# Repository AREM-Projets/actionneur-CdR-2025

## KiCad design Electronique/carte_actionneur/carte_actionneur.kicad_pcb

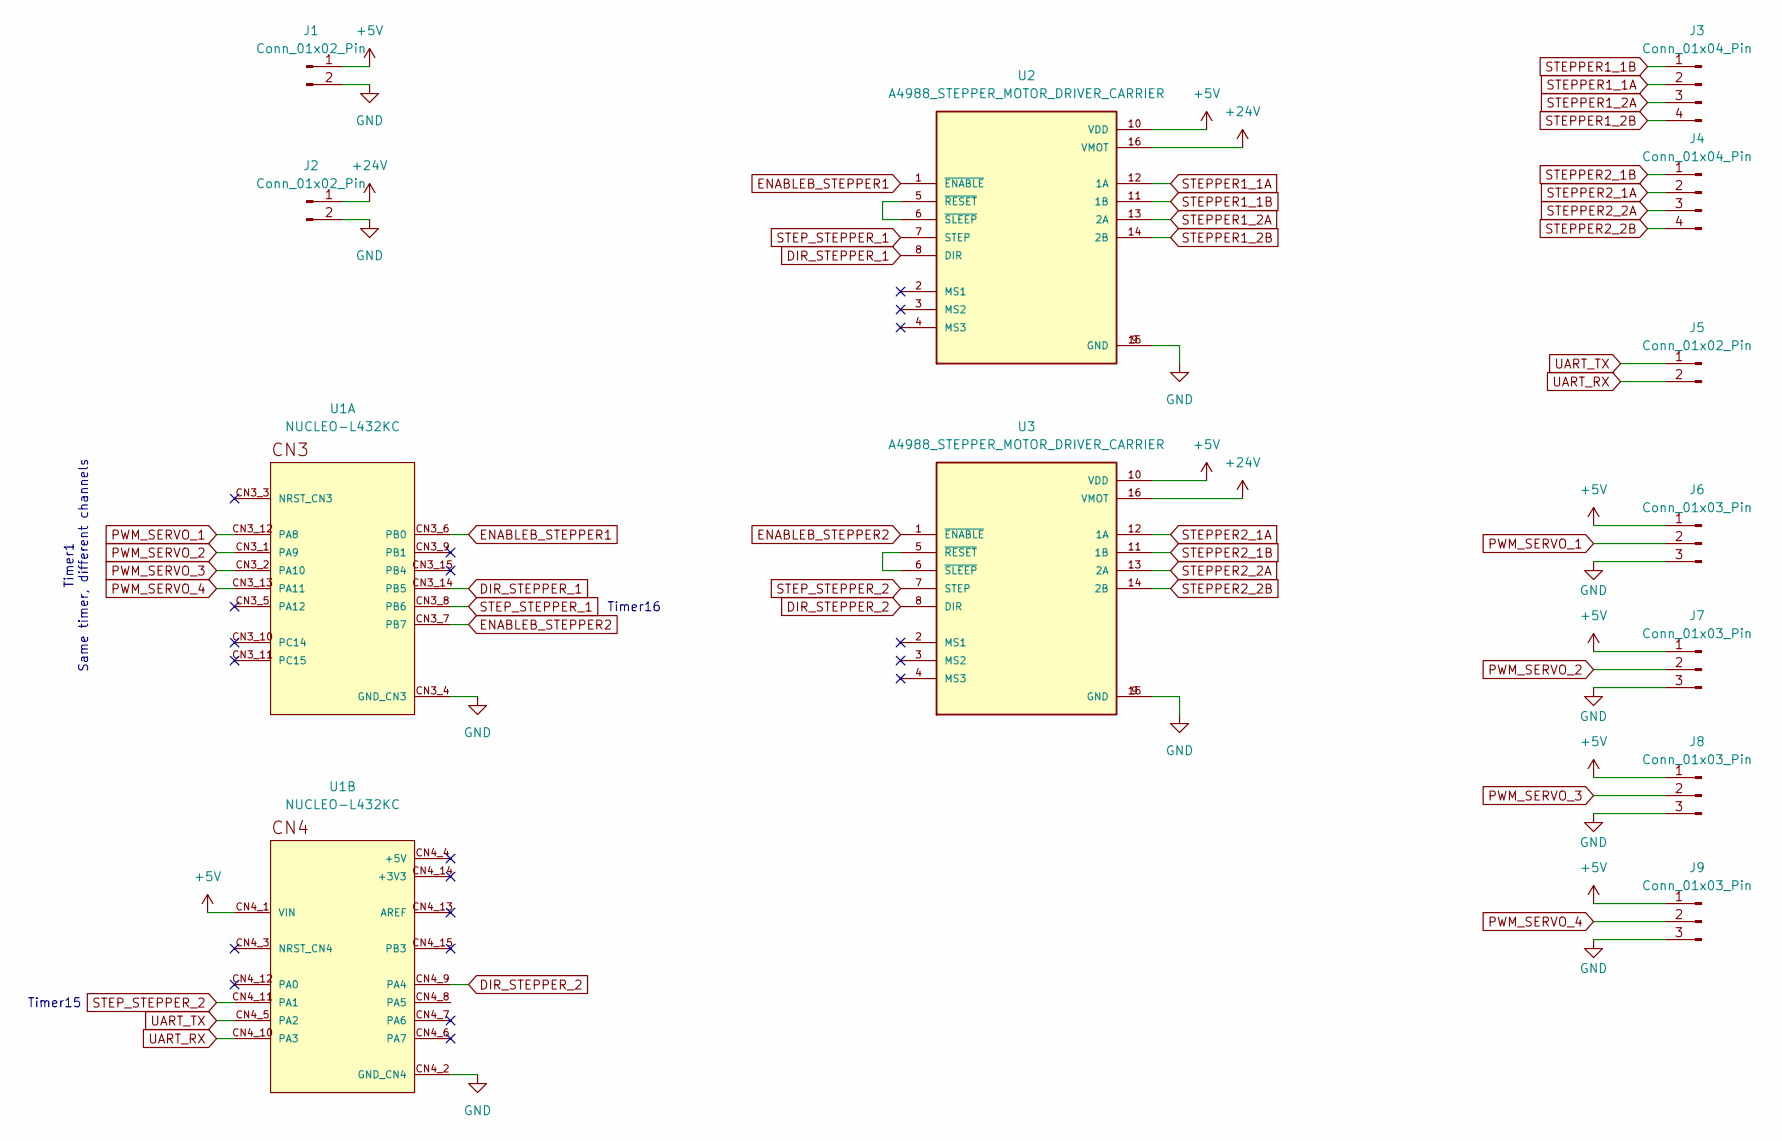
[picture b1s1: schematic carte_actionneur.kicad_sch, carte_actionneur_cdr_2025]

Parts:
J1, J2, J5: Conn_01x02_Pin; JST_EH_B2B-EH-A_1x02_P2.50mm_Vertical
J3, J4: Conn_01x04_Pin; JST_EH_B4B-EH-A_1x04_P2.50mm_Vertical
J6, J7, J8, J9: Conn_01x03_Pin; JST_EH_B3B-EH-A_1x03_P2.50mm_Vertical
U1: NUCLEO-L432KC; MODULE_NUCLEO-L432KC; PARTREV N/A
U2, U3: A4988_STEPPER_MOTOR_DRIVER_CARRIER; MODULE_A4988_STEPPER_MOTOR_DRIVER_CARRIER

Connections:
+5V: J1.1, J6.1, J7.1, J8.1, J9.1, U1.CN4_1 (VIN), U2.10 (VDD), U3.10 (VDD)
+24V: J2.1, U2.16 (VMOT), U3.16 (VMOT)
DIR_STEPPER_1: U1.CN3_14 (PB5), U2.8 (DIR)
DIR_STEPPER_2: U1.CN4_9 (PA4), U3.8 (DIR)
ENABLEB_STEPPER1: U1.CN3_6 (PB0), U2.1 (~ENABLE)
ENABLEB_STEPPER2: U1.CN3_7 (PB7), U3.1 (~ENABLE)
GND: J1.2, J2.2, J6.3, J7.3, J8.3, J9.3, U1.CN3_4 (GND_CN3), U1.CN4_2 (GND_CN4), U2.9 (GND), U2.15 (GND), U3.9 (GND), U3.15 (GND)
unnamed: U2.5 (~RESET), U2.6 (~SLEEP)
unnamed: U3.5 (~RESET), U3.6 (~SLEEP)
PWM_SERVO_1: J6.2, U1.CN3_12 (PA8)
PWM_SERVO_2: J7.2, U1.CN3_1 (PA9)
PWM_SERVO_3: J8.2, U1.CN3_2 (PA10)
PWM_SERVO_4: J9.2, U1.CN3_13 (PA11)
STEPPER1_1A: J3.2, U2.12 (1A)
STEPPER1_1B: J3.1, U2.11 (1B)
STEPPER1_2A: J3.3, U2.13 (2A)
STEPPER1_2B: J3.4, U2.14 (2B)
STEPPER2_1A: J4.2, U3.12 (1A)
STEPPER2_1B: J4.1, U3.11 (1B)
STEPPER2_2A: J4.3, U3.13 (2A)
STEPPER2_2B: J4.4, U3.14 (2B)
STEP_STEPPER_1: U1.CN3_8 (PB6), U2.7 (STEP)
STEP_STEPPER_2: U1.CN4_11 (PA1), U3.7 (STEP)
UART_RX: J5.2, U1.CN4_10 (PA3)
UART_TX: J5.1, U1.CN4_5 (PA2)

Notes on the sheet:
Timer15
Timer1 Same timer, different channels
Timer16

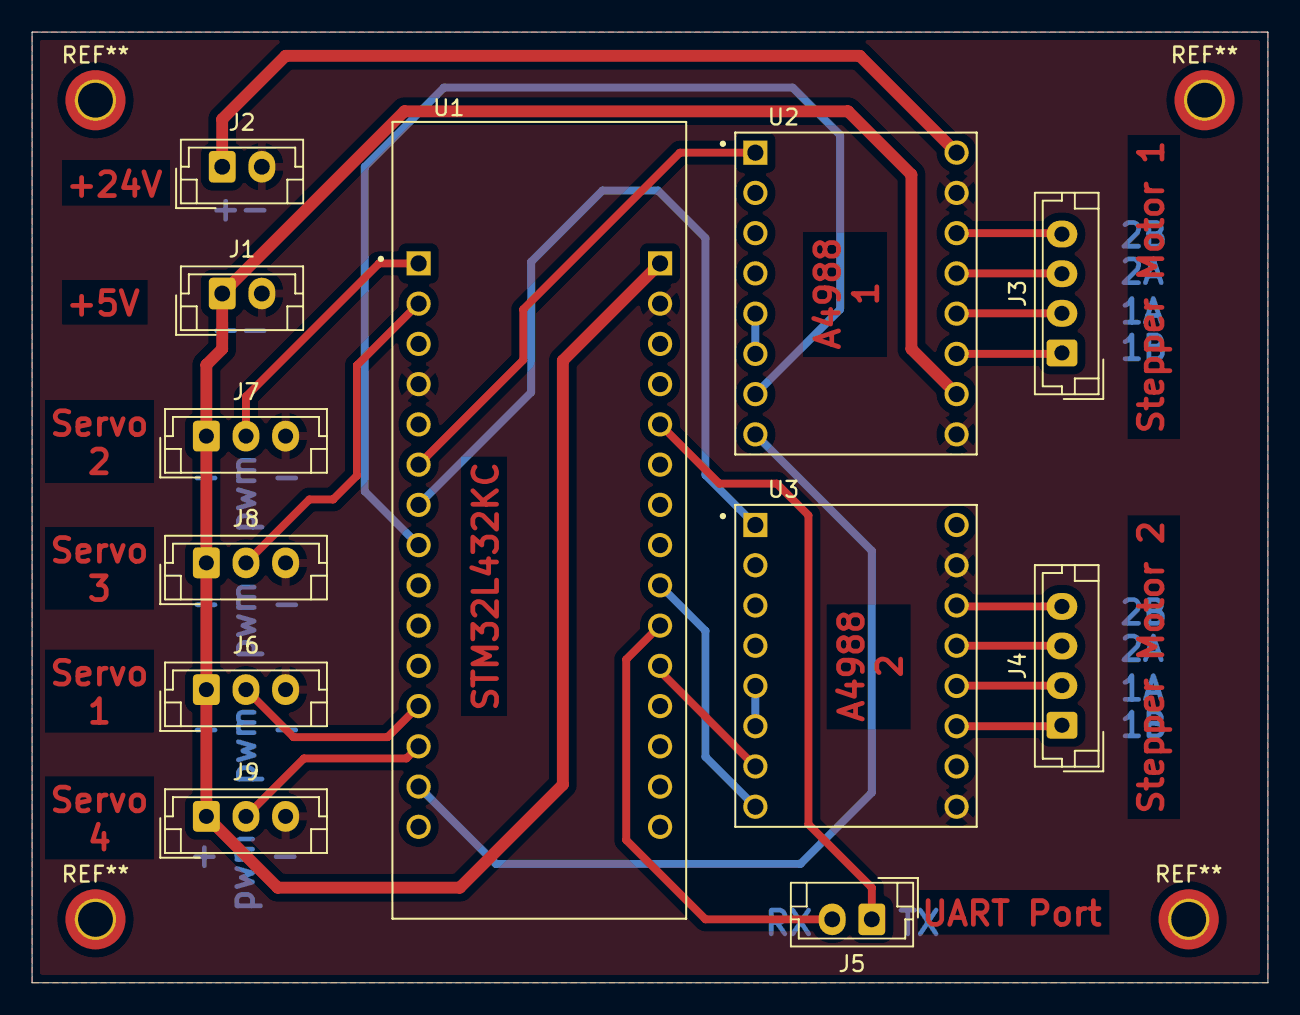
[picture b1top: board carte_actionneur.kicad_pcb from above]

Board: 2 copper layers, 78.0 x 60.0 mm, 12 parts (0 on the bottom side), 25 nets.

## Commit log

2025-05-14 add Electronique
2025-05-24 feat [servo_pwm] : add servo library
2025-05-24 fix : file name error fixed
2025-05-25 feat : an algorithm that work
